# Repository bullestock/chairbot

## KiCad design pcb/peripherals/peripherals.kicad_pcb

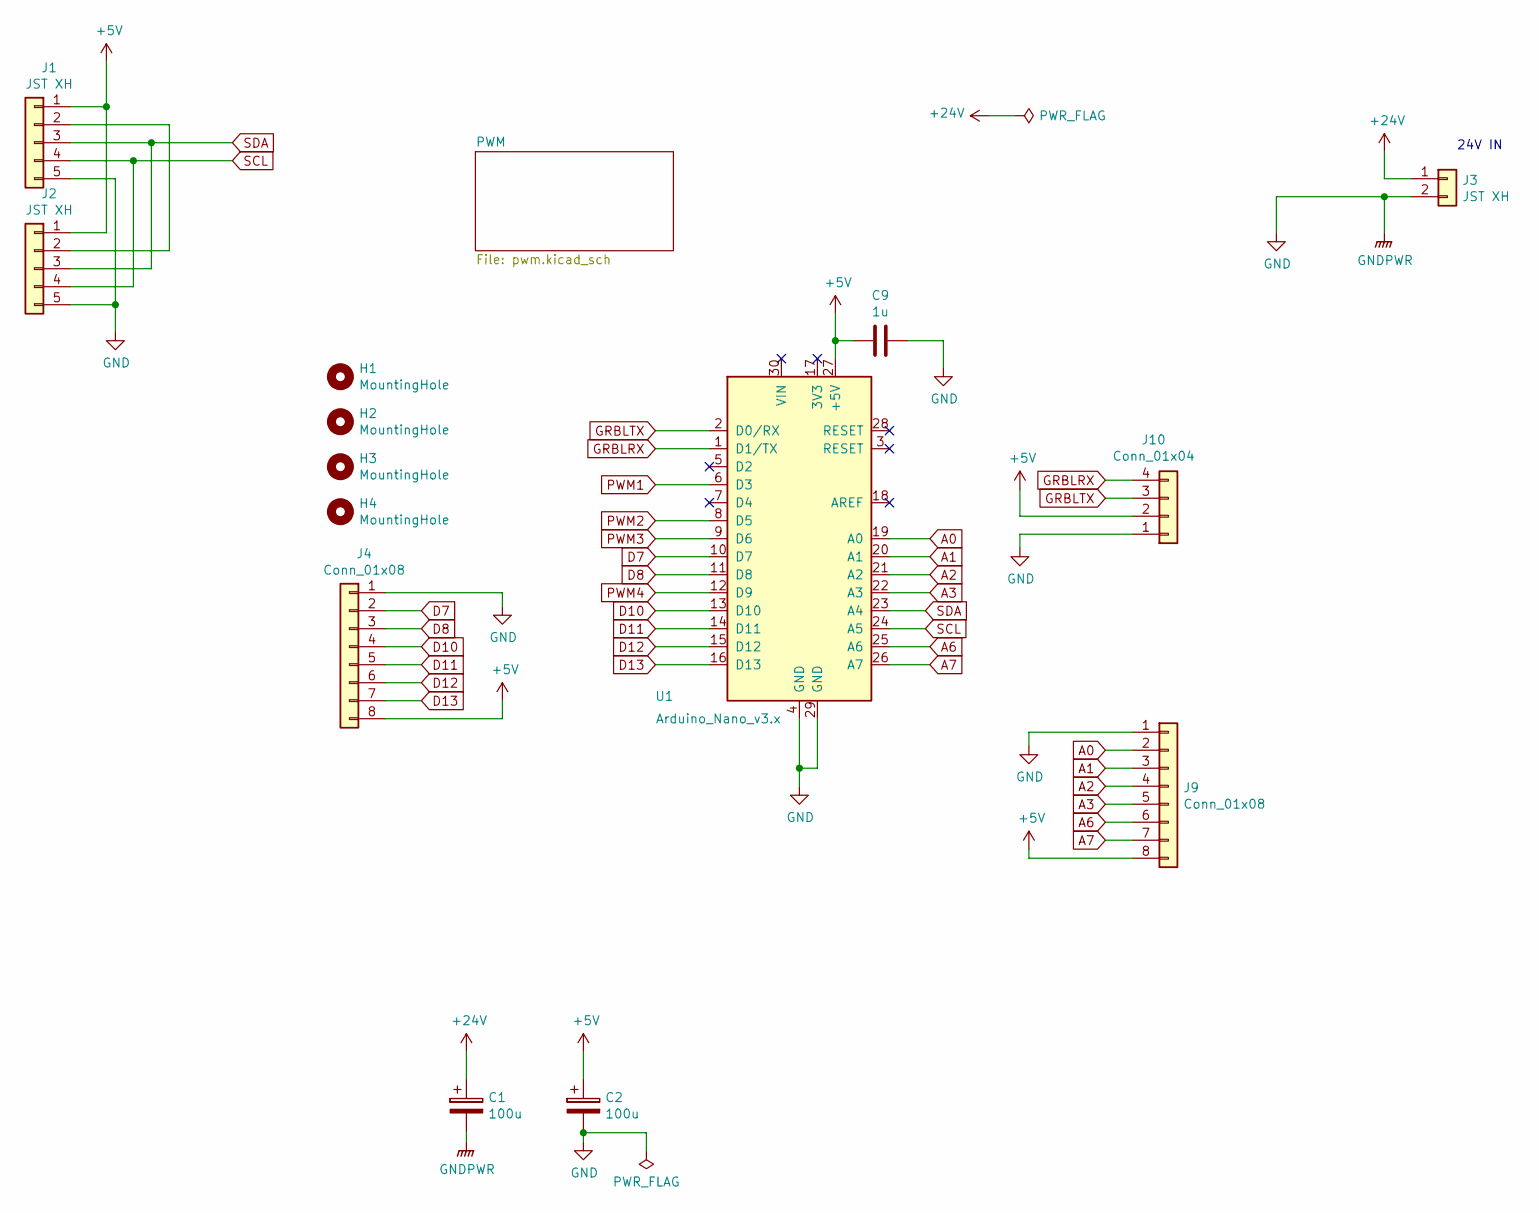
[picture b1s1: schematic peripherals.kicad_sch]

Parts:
C1, C2: 100u; CP_Elec_10x10
C9: 1u; C_0805_2012Metric
H1, H2, H3, H4: MountingHole; MountingHole_3.2mm_M3
J1, J2: JST XH; JST_XH_B05B-XH-A_1x05_P2.50mm_Vertical
J3: JST XH; JST_XH_B02B-XH-A_1x02_P2.50mm_Vertical
J4, J9: Conn_01x08; JST_XH_B08B-XH-A_1x08_P2.50mm_Vertical
J10: Conn_01x04; JST_XH_B04B-XH-A_1x04_P2.50mm_Vertical
U1: Arduino_Nano_v3.x; Arduino_Nano

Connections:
+5V: C2.1, C9.2, J1.1, J2.1, J4.8, J9.8, J10.2, U1.27 (+5V)
+24V: C1.1, J3.1; also elsewhere on the board
A0: J9.2, U1.19 (A0)
A1: J9.3, U1.20 (A1)
A2: J9.4, U1.21 (A2)
A3: J9.5, U1.22 (A3)
A6: J9.6, U1.25 (A6)
A7: J9.7, U1.26 (A7)
D7: J4.2, U1.10 (D7)
D8: J4.3, U1.11 (D8)
D10: J4.4, U1.13 (D10)
D11: J4.5, U1.14 (D11)
D12: J4.6, U1.15 (D12)
D13: J4.7, U1.16 (D13)
GND: C1.2, C2.2, C9.1, J1.5, J2.5, J3.2, J4.1, J9.1, J10.1, U1.4 (GND), U1.29 (GND); also elsewhere on the board
GRBLRX: J10.4, U1.1 (D1/TX)
GRBLTX: J10.3, U1.2 (D0/RX)
unnamed: J1.2, J2.2
PWM1: U1.6 (D3); also elsewhere on the board
PWM2: U1.8 (D5); also elsewhere on the board
PWM3: U1.9 (D6); also elsewhere on the board
PWM4: U1.12 (D9); also elsewhere on the board
SCL: J1.4, J2.4, U1.24 (A5)
SDA: J1.3, J2.3, U1.23 (A4)

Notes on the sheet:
24V IN

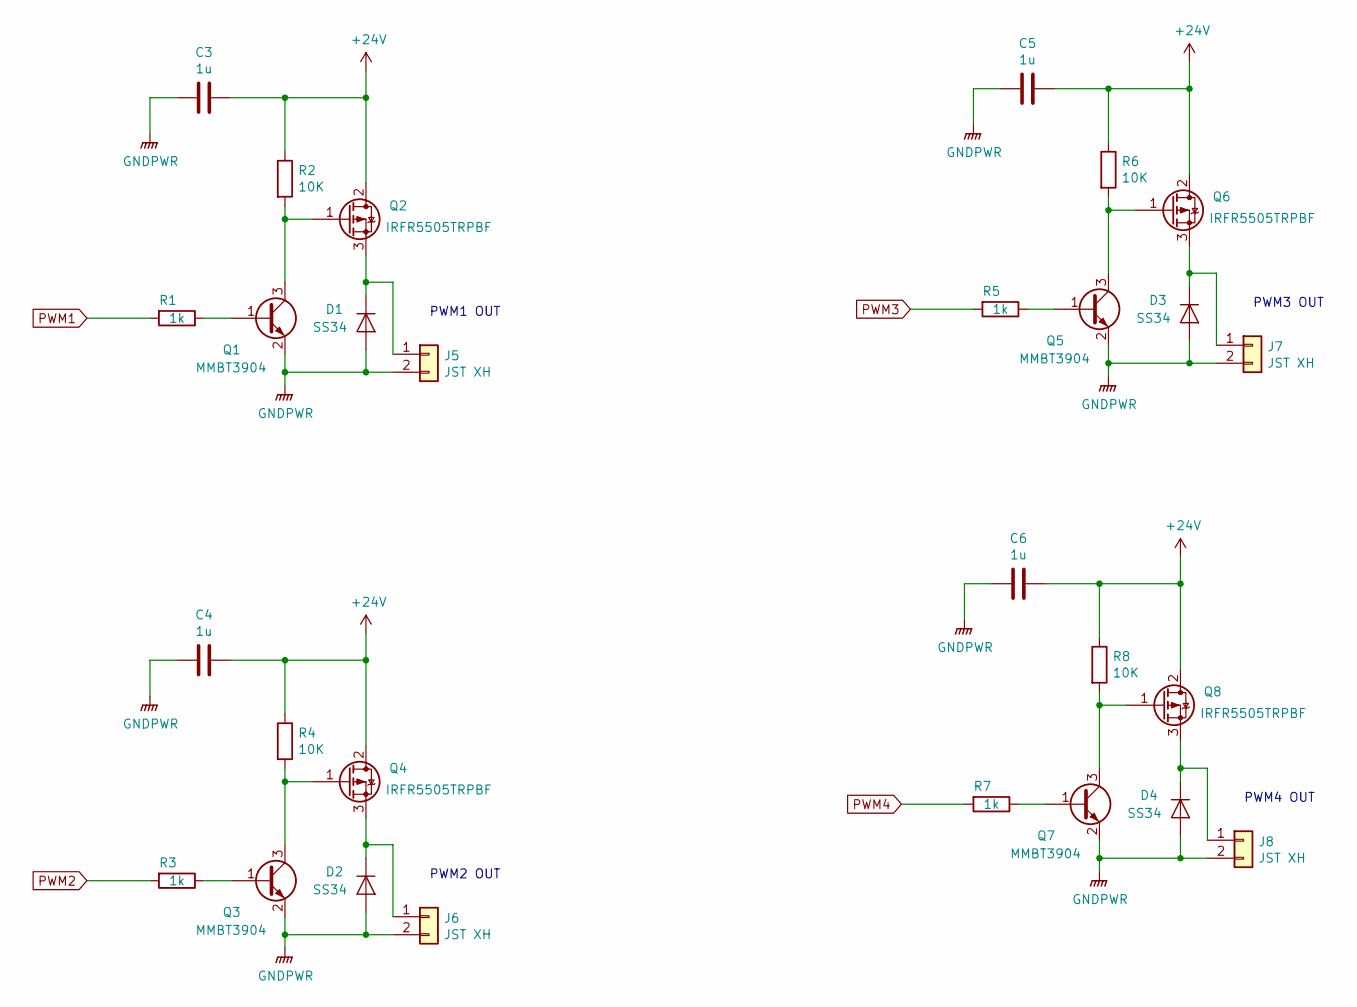
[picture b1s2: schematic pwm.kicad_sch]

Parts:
C3, C4, C5, C6: 1u; C_0805_2012Metric
D1, D2, D3, D4: SS34; D_SMB
J5, J6, J7, J8: JST XH; JST_XH_B02B-XH-A_1x02_P2.50mm_Vertical
Q1, Q3, Q5, Q7: MMBT3904; SOT-23
Q2, Q4, Q6, Q8: IRFR5505TRPBF; TO-252-3_TabPin2
R1, R3, R5, R7: 1k; R_0603_1608Metric
R2, R4, R6, R8: 10K; R_0603_1608Metric

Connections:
+24V: C3.1, C4.1, C5.1, C6.1, Q2.2 (D), Q4.2 (D), Q6.2 (D), Q8.2 (D), R2.1, R4.1, R6.1, R8.1; also elsewhere on the board
GND: C3.2, C4.2, C5.2, C6.2, D1.2 (A), D2.2 (A), D3.2 (A), D4.2 (A), J5.2, J6.2, J7.2, J8.2, Q1.2 (E), Q3.2 (E), Q5.2 (E), Q7.2 (E); also elsewhere on the board
unnamed: D1.1 (K), J5.1, Q2.3 (S)
unnamed: D2.1 (K), J6.1, Q4.3 (S)
unnamed: D3.1 (K), J7.1, Q6.3 (S)
unnamed: D4.1 (K), J8.1, Q8.3 (S)
unnamed: Q1.1 (B), R1.1
unnamed: Q1.3 (C), Q2.1 (G), R2.2
unnamed: Q3.1 (B), R3.1
unnamed: Q3.3 (C), Q4.1 (G), R4.2
unnamed: Q5.1 (B), R5.1
unnamed: Q5.3 (C), Q6.1 (G), R6.2
unnamed: Q7.1 (B), R7.1
unnamed: Q7.3 (C), Q8.1 (G), R8.2
PWM1: R1.2; also elsewhere on the board
PWM2: R3.2; also elsewhere on the board
PWM3: R5.2; also elsewhere on the board
PWM4: R7.2; also elsewhere on the board

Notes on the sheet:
PWM3 OUT
PWM1 OUT
PWM4 OUT
PWM2 OUT

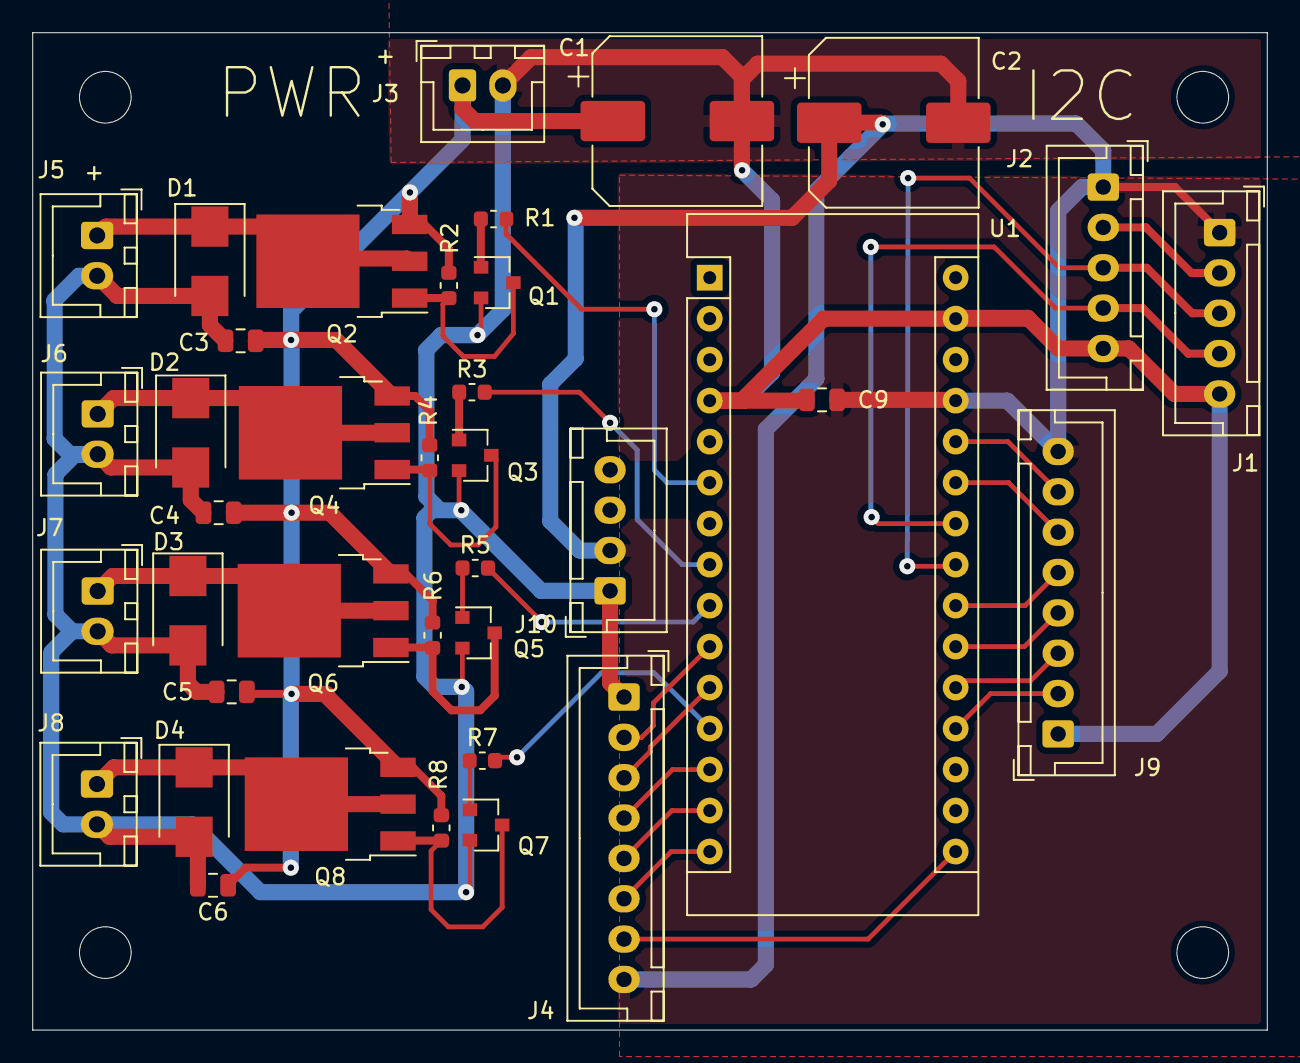
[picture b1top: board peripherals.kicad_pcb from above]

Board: 2 copper layers, 76.5 x 61.8 mm, 42 parts (0 on the bottom side), 36 nets.

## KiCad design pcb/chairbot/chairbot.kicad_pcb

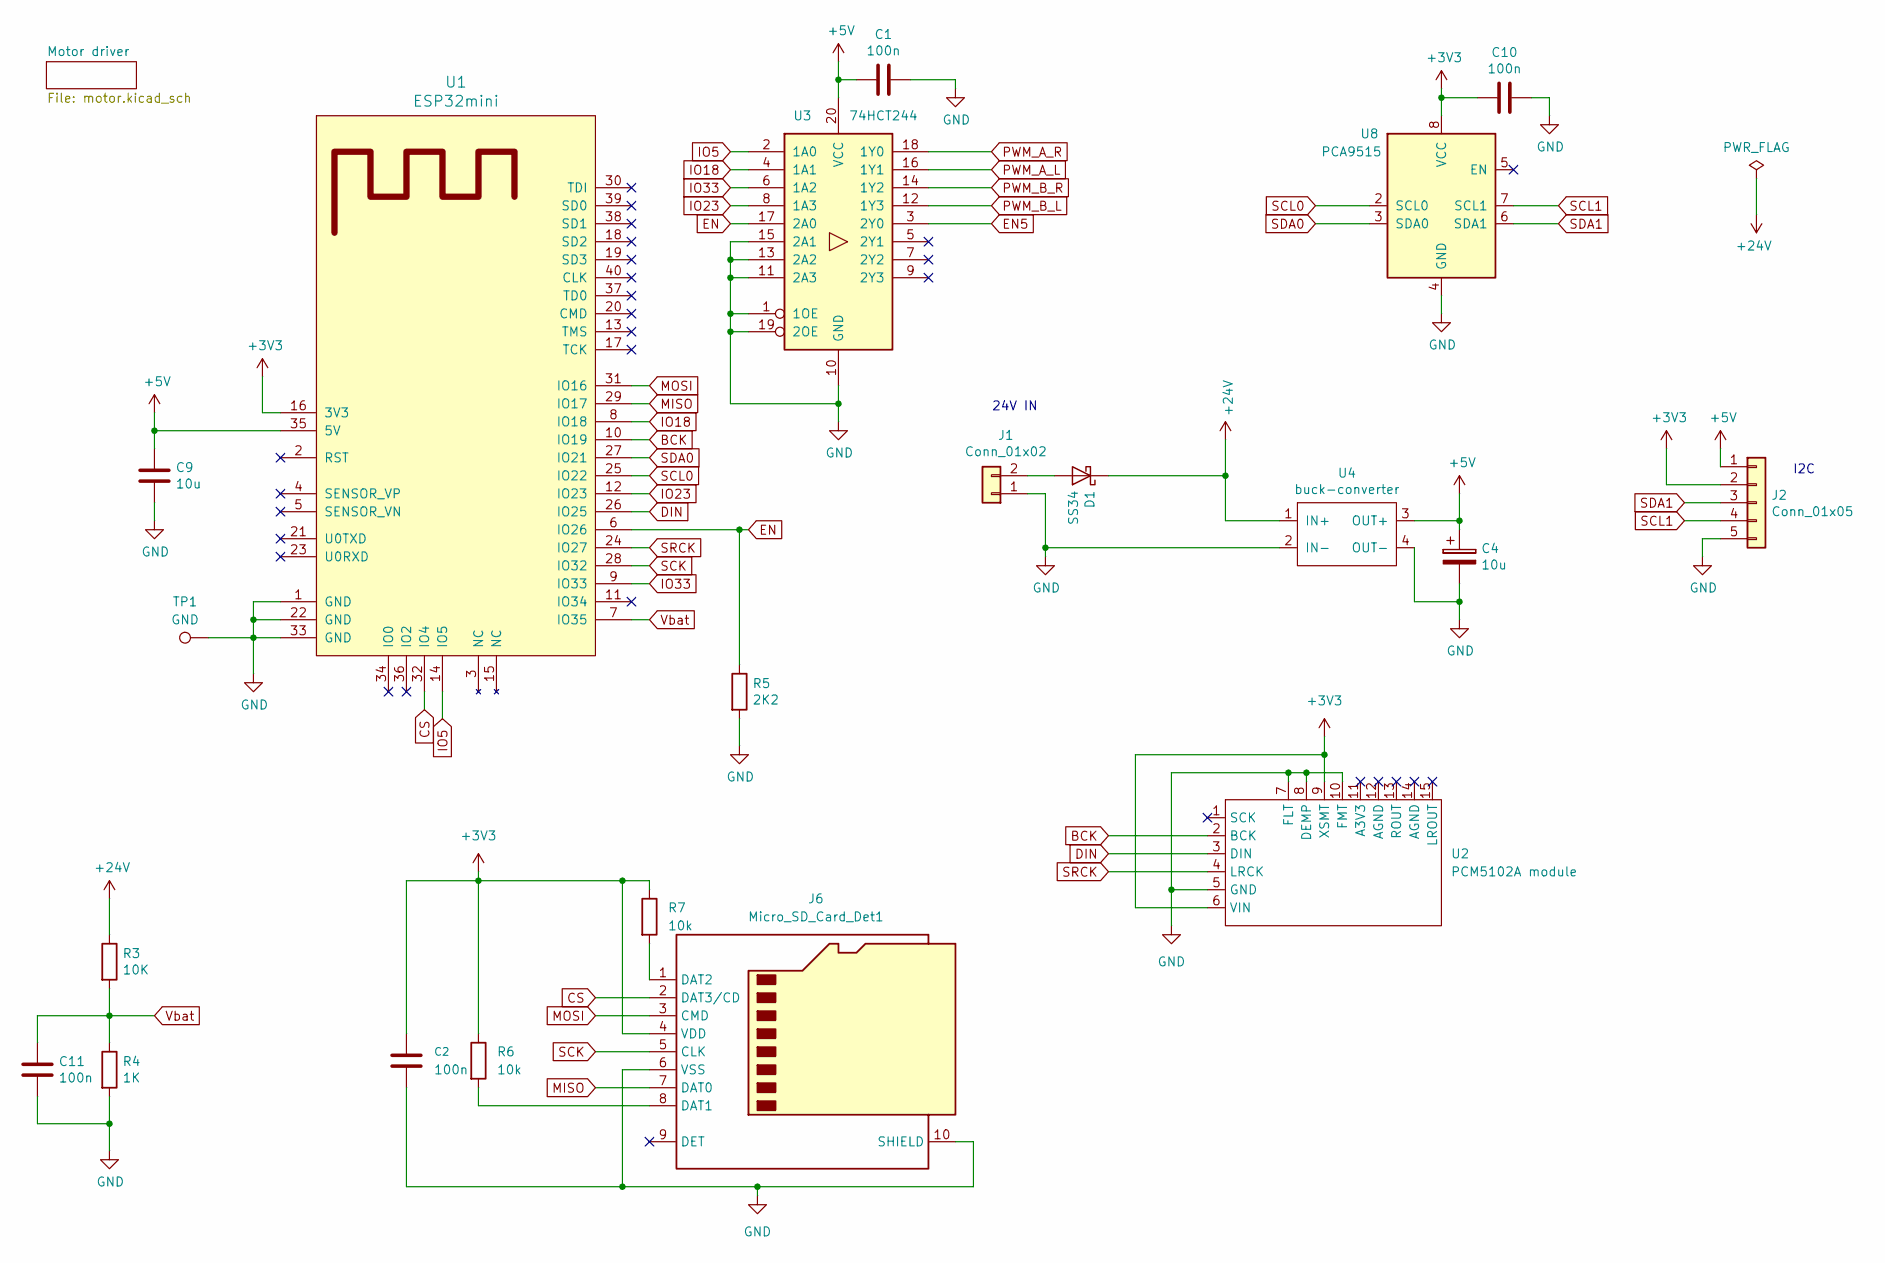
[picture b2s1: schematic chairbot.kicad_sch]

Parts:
C1, C2, C10, C11: 100n; C_0603_1608Metric
C4, C9: 10u; C_0805_2012Metric
D1: SS34; D_SMB
J1: Conn_01x02; JST_XH_B02B-XH-A_1x02_P2.50mm_Vertical
J2: Conn_01x05; JST_XH_B05B-XH-A_1x05_P2.50mm_Vertical
J6: Micro_SD_Card_Det1; J_SD_Card-micro_dual
R3: 10K; R_0603_1608Metric
R4: 1K; R_0603_1608Metric
R5: 2K2; R_0603_1608Metric
R6, R7: 10k; R_0603_1608Metric
TP1: GND; TestPoint_Loop_D1.80mm_Drill1.0mm_Beaded
U1: ESP32mini
U2: PCM5102A module
U3: 74HCT244; TSSOP-20_4.4x6.5mm_P0.65mm
U4: buck-converter
U8: PCA9515; TSSOP-8_3x3mm_P0.65mm

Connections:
+3V3: C2.1, C10.2, J2.2, J6.4 (VDD), R6.1, R7.1, U1.16 (3V3), U2.6 (VIN), U2.9 (XSMT), U8.8 (VCC)
+5V: C1.2, C4.1, C9.1, J2.1, U1.35 (5V), U3.20 (VCC), U4.3 (OUT+); also elsewhere on the board
+24V: D1.1 (K), R3.1, U4.1 (IN+); also elsewhere on the board
BCK: U1.10 (IO19), U2.2 (BCK)
CS: J6.2 (DAT3/CD), U1.32 (IO4)
DIN: U1.26 (IO25), U2.3 (DIN)
EN: R5.1, U1.6 (IO26), U3.17 (2A0)
EN5: U3.3 (2Y0); also elsewhere on the board
GND: C1.1, C2.2, C4.2, C9.2, C10.1, C11.2, J1.1, J2.5, J6.6 (VSS), J6.10 (SHIELD), R4.2, R5.2, TP1.1 (1_1), U1.1 (GND), U1.22 (GND), U1.33 (GND), U2.5 (GND), U2.7 (FLT), U2.8 (DEMP), U2.10 (FMT), U3.1 (1OE), U3.10 (GND), U3.11 (2A3), U3.13 (2A2), U3.15 (2A1), U3.19 (2OE), U4.2 (IN-), U4.4 (OUT-), U8.4 (GND); also elsewhere on the board
IO5: U1.14 (IO5), U3.2 (1A0)
IO18: U1.8 (IO18), U3.4 (1A1)
IO23: U1.12 (IO23), U3.8 (1A3)
IO33: U1.9 (IO33), U3.6 (1A2)
MISO: J6.7 (DAT0), U1.29 (IO17)
MOSI: J6.3 (CMD), U1.31 (IO16)
unnamed: D1.2 (A), J1.2
unnamed: J6.8 (DAT1), R6.2
unnamed: J6.1 (DAT2), R7.2
PWM_A_L: U3.16 (1Y1); also elsewhere on the board
PWM_A_R: U3.18 (1Y0); also elsewhere on the board
PWM_B_L: U3.12 (1Y3); also elsewhere on the board
PWM_B_R: U3.14 (1Y2); also elsewhere on the board
SCK: J6.5 (CLK), U1.28 (IO32)
SCL0: U1.25 (IO22), U8.2 (SCL0)
SCL1: J2.4, U8.7 (SCL1)
SDA0: U1.27 (IO21), U8.3 (SDA0)
SDA1: J2.3, U8.6 (SDA1)
SRCK: U1.24 (IO27), U2.4 (LRCK)
Vbat: C11.1, R3.2, R4.1, U1.7 (IO35)

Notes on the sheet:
I2C
24V IN

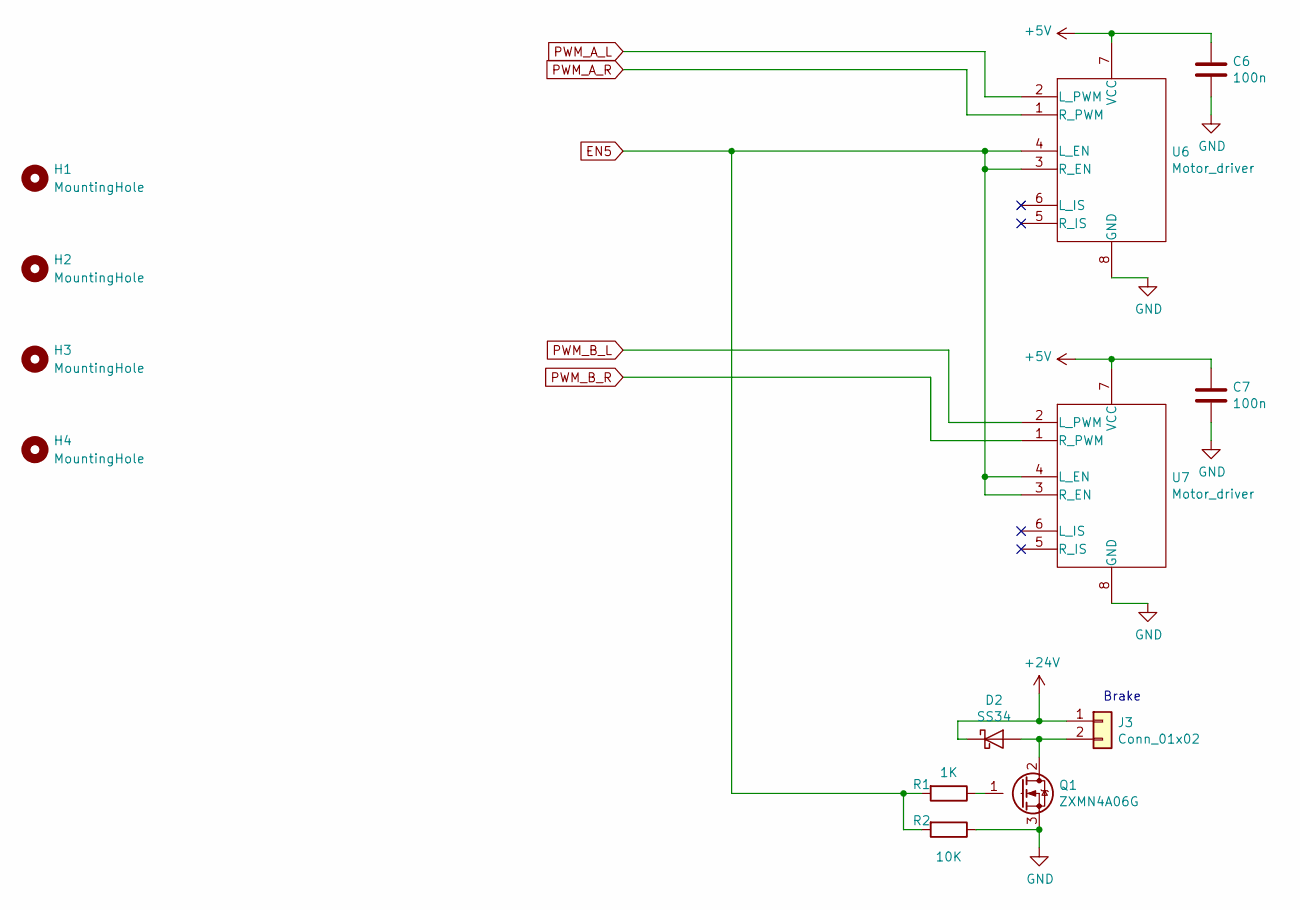
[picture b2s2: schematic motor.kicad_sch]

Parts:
C6, C7: 100n; C_0603_1608Metric
D2: SS34; D_SMB
H1, H2, H3, H4: MountingHole; MountingHole_3.2mm_M3
J3: Conn_01x02; JST_XH_B02B-XH-A_1x02_P2.50mm_Vertical
Q1: ZXMN4A06G; SOT-223-3_TabPin2
R1: 1K; R_0603_1608Metric
R2: 10K; R_0603_1608Metric
U6, U7: Motor_driver; PinSocket_2x04_P2.54mm_Horizontal

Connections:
+5V: C6.1, C7.1, U6.7 (VCC), U7.7 (VCC); also elsewhere on the board
+24V: D2.1 (K), J3.1; also elsewhere on the board
EN5: R1.2, R2.2, U6.3 (R_EN), U6.4 (L_EN), U7.3 (R_EN), U7.4 (L_EN); also elsewhere on the board
GND: C6.2, C7.2, Q1.3 (S), R2.1, U6.8 (GND), U7.8 (GND); also elsewhere on the board
unnamed: D2.2 (A), J3.2, Q1.2 (D)
unnamed: Q1.1 (G), R1.1
PWM_A_L: U6.2 (L_PWM); also elsewhere on the board
PWM_A_R: U6.1 (R_PWM); also elsewhere on the board
PWM_B_L: U7.2 (L_PWM); also elsewhere on the board
PWM_B_R: U7.1 (R_PWM); also elsewhere on the board

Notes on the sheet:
Brake

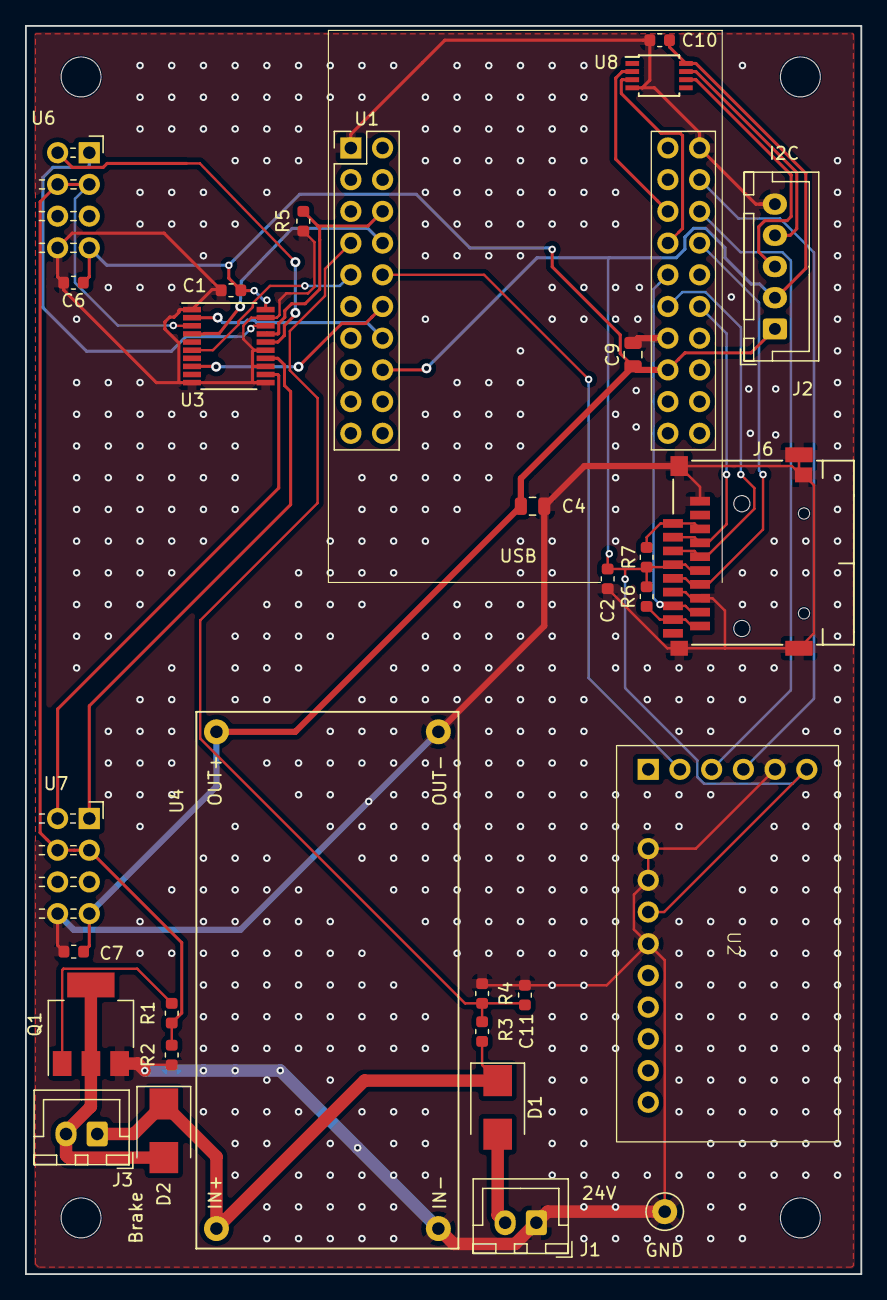
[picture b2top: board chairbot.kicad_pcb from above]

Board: 2 copper layers, 66.9 x 100.0 mm, 34 parts (0 on the bottom side), 31 nets.

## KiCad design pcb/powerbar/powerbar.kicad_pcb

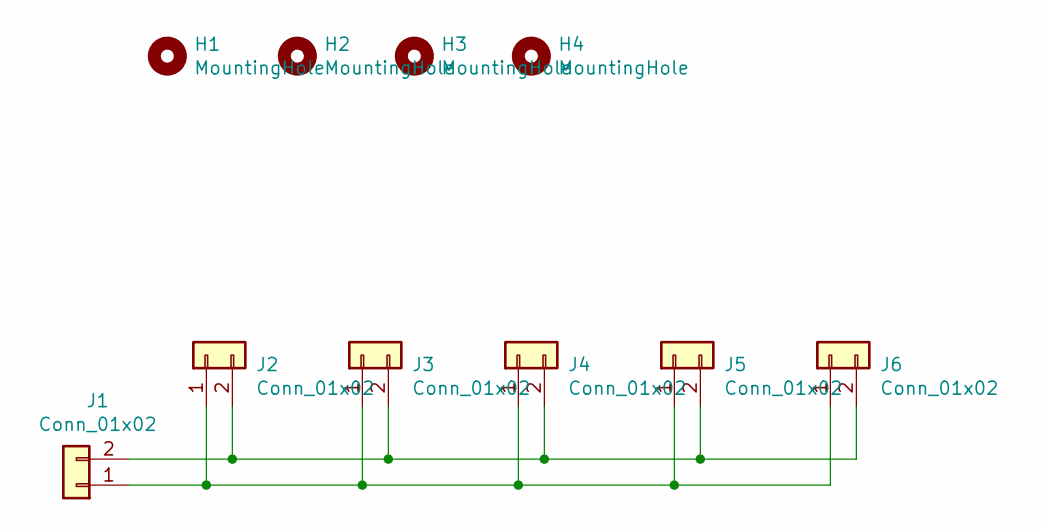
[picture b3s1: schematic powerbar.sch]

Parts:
H1, H2, H3, H4: MountingHole; MountingHole_3.2mm_M3
J1: Conn_01x02; PhoenixContact_MCV_1,5_2-G-5.08_1x02_P5.08mm_Vertical
J2, J3, J4, J5, J6: Conn_01x02; JST_XH_B02B-XH-A_1x02_P2.50mm_Vertical

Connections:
unnamed: J1.1, J2.1, J3.1, J4.1, J5.1, J6.1
unnamed: J1.2, J2.2, J3.2, J4.2, J5.2, J6.2

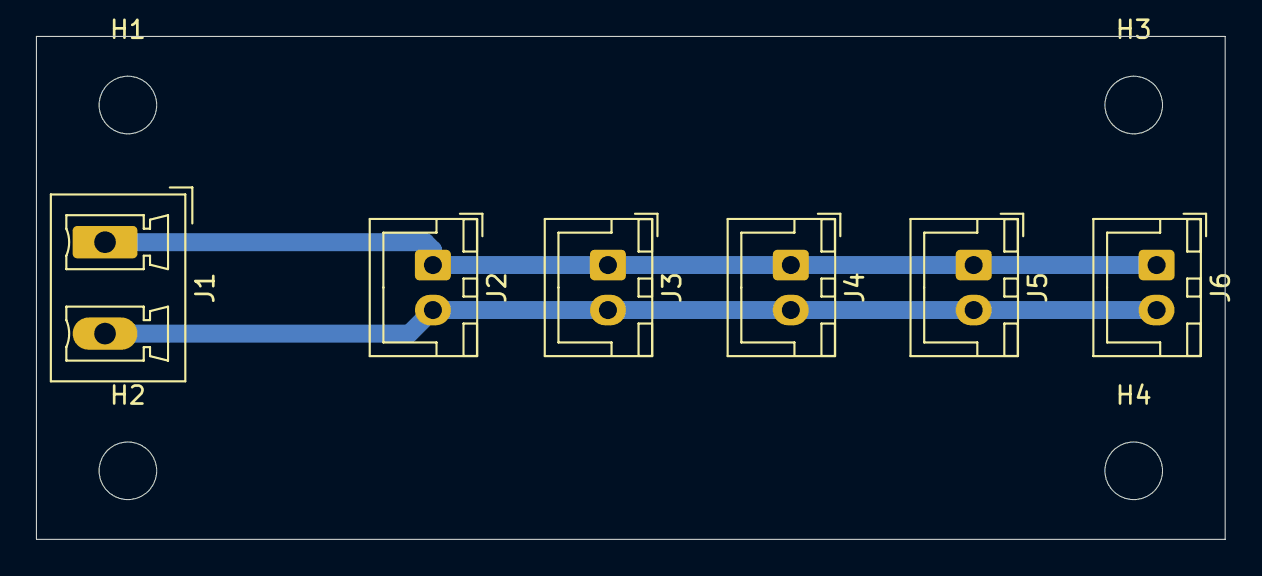
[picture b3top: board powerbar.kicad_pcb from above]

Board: 2 copper layers, 66.0 x 27.9 mm, 10 parts (0 on the bottom side), 2 nets.

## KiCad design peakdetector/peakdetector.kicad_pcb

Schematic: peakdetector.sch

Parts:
C1, C2, C3: 220n; C_0603
D1, D2, D3, D4: BAT54; D_SOT-23_ANK
J1: Conn_01x07_Male; Pin_Header_Straight_1x07_Pitch2.54mm
R1, R2: 100K; R_0603
U1: TL074; SOP14

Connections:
+5V: C3.1, J1.7, U1.4 (V+)
GND: C1.2, C2.2, C3.2, D1.2, D2.2, J1.1, R1.2, R2.2, U1.11 (V-)
unnamed: C1.1, D3.1, R1.1, U1.2 (-), U1.5 (+)
unnamed: C2.1, D4.1, R2.1, U1.9 (-), U1.12 (+)
unnamed: D1.1, D3.2, U1.1
unnamed: D2.1, D4.2, U1.8
unnamed: J1.2, U1.3 (+)
unnamed: J1.3, U1.6 (-), U1.7
unnamed: J1.4, U1.10 (+)
unnamed: J1.5, U1.13 (-), U1.14

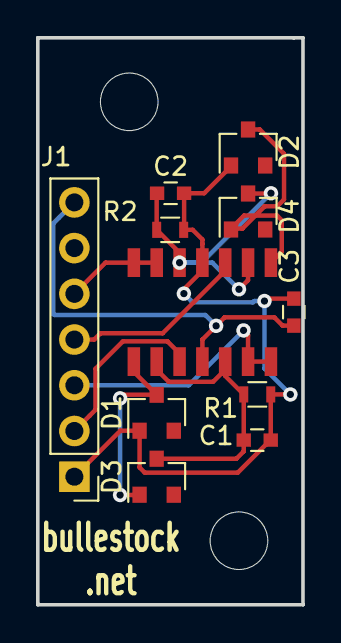
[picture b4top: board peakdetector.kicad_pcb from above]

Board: 2 copper layers, 14.7 x 31.5 mm, 11 parts (0 on the bottom side), 10 nets.

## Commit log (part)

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2016-07-29 Initial commit.
2016-08-18 First working version.
2016-08-18 Add argument validation.
2016-08-25 Controller process for Pi.
2016-08-30 Add test code.
2016-08-30 Add Makefile.
2016-09-06 Add startup script.
2016-09-06 Wait until joystick device is ready.
2016-09-06 Use dedicated LCD device; add check for Bluetooth device.
2016-09-06 udev rules for LCD and USB/serial.
2016-09-06 Use specific portname.
2016-09-06 Show battery voltage on LCD.
2016-09-06 Use correct PWM pins; add V command.
2016-09-06 Move LCD updating to separate script.
2016-09-06 Fix path to updatelcd.
2016-09-08 Read motor controller response.
2016-09-08 Use specific port.
2016-09-08 Add dead man's switch.
2016-09-11 If Ethernet is not up, show WiFi IP address.
2016-09-13 Limit power.
2016-09-13 Adjust voltage sense scale factor.
2016-09-13 Do not start controller if 'noautostart' exists.
2016-09-14 Read joystick.
2016-09-14 Add LCD control.
2016-09-14 Open motor driver.
2016-09-15 Add missing parens.
2016-09-15 First working Python version.
2016-09-16 Add options to run without LCD and/or motor driver.
2016-09-16 Use Python controller.
2016-09-16 Handle 'no network' scenario.
2016-09-16 Update IP address.
2016-09-17 LCD driver class.
2016-09-17 Use LCD driver class.
2016-09-17 Move joystick code to separate class.
2016-09-18 Set MAX_IDLE_COUNT properly.
2016-09-18 Add progress indicator.
2016-09-20 Add missing argument to show_voltage().
2016-09-20 Fix bugs.
2016-09-20 Use select().
2016-09-20 Make main loop more responsive. Set minimum power limit.
2016-09-20 Tune PWM.
2016-09-20 Limit power; increase responsiveness.
2016-09-20 Add countdown.
2016-09-22 Remove C++ code.
2016-09-22 Show status.
2016-09-22 Show status; improve limiting; tune.
2016-09-22 Improve throughput.
2016-09-24 Set initial angles.
2016-09-24 Rename M to G; add M command for smooth motion.
2016-09-29 Add rule for robot arm controller.
2016-09-29 Autodetect serial ports.
2016-09-29 Add identifier in output.
2016-09-29 Do not use symlinks.
2016-09-29 Add limiting.
2016-09-29 Add rudimentary arm control.
2016-10-02 Configuration for motion daemon.
2016-10-05 Respond faster to connect.
2016-10-05 Fix limit bug.
2016-10-05 Adjust limits.
2016-10-05 Improve autodetection of ports. Change handling of arm.
2016-10-05 Make LCD work again. Reimplement arm control.
2016-10-05 Restrict arm1 movement based on arm2.
2016-10-06 Add fourth servo.
2016-10-06 Add gripper control.
2016-10-07 I2C.
2016-10-08 Dummy sixaxis driver.
2016-10-08 Make test work.
2016-10-08 Catch exceptions.
2016-10-08 Play with pivot.
2016-10-08 Implement web framework.
2016-10-08 Increase MAX_IDLE_COUNT to compensate for increased time frequency.
2016-10-08 Implement emergency stop.
2016-10-08 Implement powerup.
2016-10-08 Polish web interface.
2016-10-08 Add support for I2C.
2016-10-08 Use binary procotol.
2016-10-09 Implement I2C correctly.
2016-10-09 Implement I2C interface.
2016-10-09 Use I2C for motor and arm control.
2016-10-09 Remove serial output from I2C.
2016-10-12 LED swag.
2016-10-12 Improve palette switching.
2016-10-12 Add more modes.
2016-10-12 Add I2C interface.
2017-06-11 Use only one pin for enable.
2017-06-18 Test motor control via I2C.
2017-08-09 Update.
2017-08-09 Use a single pin for both enable inputs.
2017-08-09 Skeleton for nRF24 controller.
2017-08-09 Show joystick values.
2017-08-18 Add I2C control.
2017-08-18 Rudimentary motor control
2017-08-18 Modularize.
2017-08-18 Zero sticks on startup.
2017-08-19 Show switches.
2017-08-21 Change node addresses.
2017-09-16 Control pivot with right pot.
2017-09-16 Halt motors if no data received from radio for 100 ms.
2017-09-16 Remove old controller.
2017-09-20 Measure battery voltage.
2017-09-22 Make reading of battery voltage work.
2017-09-22 Send battery voltage as a single byte.
2017-09-22 Average battery readings.
2017-09-24 Add -motortest option.
2017-09-24 Decrease MAX_IDLE_COUNT.
2017-09-25 Proof of concept.
2017-09-26 Add sound and lights control.
2017-09-26 Add signals controller.
2017-09-30 Set pinmode for MOSFET pin.
2017-09-30 Add CRC to protocol.
2017-09-30 Add missing source file.
2017-09-30 Fix bug in setting CRC.
2017-09-30 Add flash command.
2017-09-30 Flash lights when toggle switch is down.
2017-10-02 Add support for setting PWM frequency.
2017-10-02 Add support for heartbeat.
2017-10-02 Add heartbeat.
2017-10-02 Improve halting algorithm.
2017-10-02 Improve error reporting.
2017-10-08 Fix X-axis swap.
2017-10-26 Disable automatic zeroing.
2017-11-02 Fix pivot range.
2017-11-02 Apply S curve.
2017-11-16 Make left pot adjust max power.
2017-11-16 Add PWM frequency API.
2017-12-09 First attempt.
2018-08-09 Use correct analog inputs.
2018-08-17 Play around with current sense.
2018-08-17 New version.
2018-08-17 Add peak detector circuit and PCB.
2018-10-15 Hack for MMF2018.
2018-10-15 Switch to LM324.
2018-10-15 New controller board.
2018-10-24 Work on schematic.
2018-10-25 Add nRF24L01.
2018-10-26 Work.
2018-10-26 Work work work.
2018-10-27 Move outline to correct layer.
2018-10-27 Add remaining connections.
2018-11-01 Work on PCB.
2018-11-03 Finish routing.
2018-11-13 Add proper footprint for peak detector.
2018-11-17 Do more routing.
2018-11-20 Finalize layout.
2019-04-06 Blink the LED.
2019-04-06 Implement motor test.
2019-04-07 Final version.
2019-04-07 Add room for antenna connector.
2019-04-07 PCB mount.
2019-04-07 Move MISO from IO0 to IO27.
2019-04-07 Fix footprint for diodes.
2019-04-08 Attempt to talk to nRF24L01.
2019-04-08 Talk to the nRF24L01.
2019-04-11 Try to talk to the remote.
2019-04-12 Use the RF24 library with Kolban's adaptions.
2019-04-12 Implement protocol handling.
2019-04-14 Add test interface.
2019-04-14 Add support for repeating motor test.
2019-04-16 Fix various issues.
2019-04-16 Handle brake.
2019-04-16 Add I2C scan.
2019-04-17 Fix more stuff.
2019-05-05 Clean up.
2019-05-05 Add battery measurement.
2019-05-05 Add flanges.
2019-05-06 Limit acceleration.
2019-05-06 Enable motors.
2019-05-07 First version.
2019-06-30 Add I2C board.
2019-07-01 Tweak pin numbers.
2019-07-01 Start PCB layout.
2019-07-01 Route more tracks.
2019-07-02 Complete routing.
2019-07-21 Add PWM1/2 control.
2019-07-28 Tune motor PWM frequency; make toggle more responsive.
2019-07-28 Fix sign bug.
2019-07-28 Extend i2c command; add peripherals command.
2019-07-28 Use unique_ptr.
2019-07-28 Add console support functions.
2019-08-10 Add support for multiple banks of sounds.
2019-08-24 Add stop play command.
2019-08-24 Add stop play command.
    Fix sounds per bank.
2019-08-25 Fix sounds per bank.
2019-08-25 Fix sound bug; increase PWM2 frequency.
2019-08-25 Play sound from different banks according to button.
2019-08-25 Fix stering sign.
2019-08-25 Add argument.
2019-08-25 Add sound bank argument.
2019-09-21 Make a task for playing sound to avoid halting main control loop.
2019-09-21 Handle all I2C communication in separate task.
2019-10-13 Fix pivot overflow bug; invert steering.
2019-10-20 SMD version.
2019-10-24 Speaker box.
2019-11-15 Update for esp-idf master.
2019-11-15 Do not include deprecated esp_event_loop.h.
2019-11-18 Fix ADC attenuation setting.
2019-11-18 Add fudge factor.
2019-11-18 Remove debug.
2019-11-21 Improve steering.
2019-11-22 Fix pin numbers.
2019-11-22 Adapt for new speakers.
2019-11-23 Power distribution.
2020-01-11 Second version.
2020-09-17 Add argument to sound command.
2020-09-17 Update for new protocol.
2020-10-01 Add support for all 4 PWM outputs.
2020-10-03 Add '3' command to play sound X from bank Y.
2020-10-03 Remove DFPlayer.
2020-10-08 Clamp low power levels to zero.
2020-10-08 Adjust pivot range. Add flashing lights.
2020-10-08 Update to match peripherals firmware.
2020-10-09 Work on layout.
2020-12-26 Update for YX5300 module.
2021-07-29 Update for ESP-IDF 4.3.
2021-07-29 Increase max_radio_idle_time.
2021-08-10 Swap RX and TX.
2021-08-10 Set up for WAVGAT chip.
2021-08-10 Show received data in debug mode.
2021-08-14 Fix MOSFET polarity.
2021-08-14 Simplify sound handling.
2021-09-09 Add volume command.
2021-09-09 Update controls.
2021-09-30 Add auto zero of right stick.
2021-09-30 Add LED test command.
2021-11-04 Add stuff.
2022-01-02 Fix 3D models.
2024-09-02 Start porting to new radio driver.
2024-09-02 Rewrite motor driver to use LEDC.
2024-09-03 Update ADC code for ESP-IDF 5.
2024-09-07 Start porting to new I2C driver.
2024-09-07 Fix nRF pin defs.
2024-09-07 Do not use LED on GPIO22.
2024-09-08 Fix radio handling.
2024-09-08 Fix deprecation warnings.
2024-09-08 Cleanup.
2024-09-08 Port I2C console commands to new driver.
2024-09-12 Adapt i2c write to the simple protocol used by peripherals.ino.
2024-09-18 Add mirf component, update I2C code.
2024-09-18 Fix LEDC timer parameter.
2024-09-18 Fix copy-paste error.
2024-11-01 Add NVS support.
2024-11-03 Convert to ESPNOW.
2024-11-16 Change toggles field to 8 bits.
2024-12-05 Fix motor PWM scaling.
2024-12-20 Add debug.
2024-12-20 Fix I2C handling.
2025-01-04 Rewrite radio handling. Avoid addressing peripherals if they are not present.
2025-01-06 Improve zeroing algorithm.
2025-02-08 Update KiCAD version.
2025-02-09 Provide visual feedback, add timeout if MP3 player does not respond.
2025-02-20 Only send changes over I2C bus.
2025-02-27 Fix assumption that maximum analog value is 255.
2025-03-16 Add support for setting own MAC.
2025-03-20 Fix max_power calculation.
2025-04-17 Implement new joystick mapping algorithm.
2025-04-17 Rewrite clamping.
2025-04-17 Use max_power.
2025-04-17 Add sounds from lockdownremote.
2025-04-19 Update to match new remote protocol format.
2025-04-21 Arm beta axis.
2025-04-24 Add check for magic value.
2025-05-24 Mount for endstop.
2025-05-24 Bump for hitting endstop.
2025-05-24 Tweak
2025-06-08 Add/move stuff.
2025-12-12 Simple bracket.
2025-12-13 Bearing mounts.
2025-12-13 Support for bearings.
2025-12-13 Add decorative holes.
2026-01-01 Add files from SD card.
2026-01-02 Tweak.
2026-01-02 Add sounds partition.
2026-01-02 Enlarge sound partition.
2026-01-02 Start updating for stateful remote.
2026-01-02 Avoid WDT reset.
2026-01-09 Add I2S sound library.
2026-01-11 Add cutout, mounting holes for stepper.
2026-01-11 Add missing files.
2026-01-13 Base.
2026-01-13 Part inside bearing.
2026-01-14 Outer bearing adapter.
2026-01-16 Fix hole positions, remove base mount holes.
2026-01-16 Rename.
2026-01-16 Increase height by 3 mm.
2026-01-16 Right hand version.
2026-01-16 Adjust crush rib size.
2026-02-14 Add.
2026-03-28 Box for counterweight.
2026-03-28 Complete.
2026-03-29 Update for geared stepper.
2026-04-01 Save new empty module before KiCAD fucks it up.
2026-04-01 Add first row of pads.
2026-04-01 Complete overall schematic.
2026-04-01 Fix errors.
2026-04-01 Add zones.
2026-04-03 Final touches.
2026-04-03 Order.
2026-04-05 Remove old speaker component. Update for ESP-IDF v6. Update GPIO allocations.
2026-04-05 Add new components.
2026-04-05 Add support for UART passthrough.
2026-04-05 Remove SerialMP3Player.
2026-04-08 Add UART support.
2026-04-08 Add UART read support.
2026-04-08 Route UART to J10.
2026-04-22 Fix UART read.
2026-04-26 Update ESP-IDF.
2026-04-26 Add missing file.
2026-04-26 Add i2s_audio.cpp.
2026-05-17 Remove obsolete peripherals commands.
2026-05-23 Attribution.
2026-05-23 Add console sound support.
2026-05-23 Update for new PCB.
2026-05-23 Add support for listing files on SD card.
2026-05-23 Fix playback of short files.
2026-05-24 Use proper filenames.
2026-05-24 Fix audio bugs, convert WAV files to stereo.
2026-05-24 Add 'sound check' command.
2026-05-24 Improve 'sound check' command; fix sound files.
2026-05-24 Update protocol.
2026-05-24 Add 'sound volume' command.
2026-05-25 Only send tracks on request.
2026-05-25 Stick for pressing boot button on remote.
2026-05-25 Fix code after protocol update.
2026-05-25 Add PWM argument validation.
2026-05-25 Sort track list.
2026-06-01 Split effects and music.
2026-06-01 Fix leading slash in track names.
